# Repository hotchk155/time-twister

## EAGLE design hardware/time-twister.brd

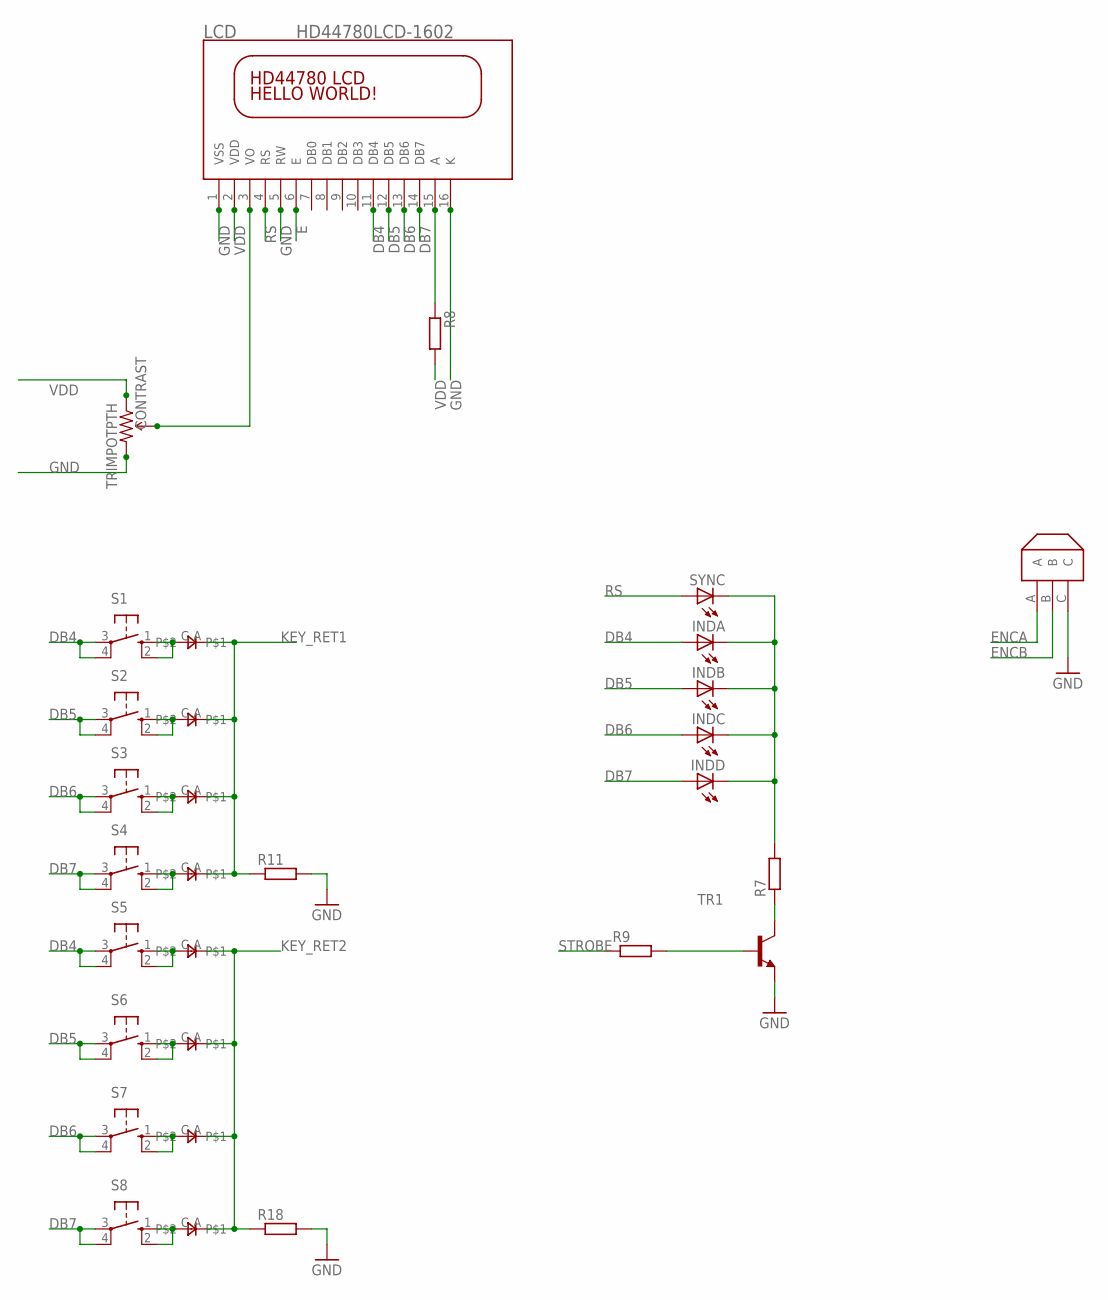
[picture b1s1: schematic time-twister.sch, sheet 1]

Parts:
CONTRAST: TRIMPOTPTH; TRIM_POT_PTH
D5, D6, D7, D8, D10, D11, D12, D13: 0805DIODE
ENC1: ENCODER
INDA: LED3MM
INDB: LED3MM
INDC: LED3MM
INDD: LED3MM
LCD: HD44780LCD-1602; LCD1602
R7, R8, R9, R11, R18: R-EU_R0805; R0805
S1, S2, S3, S4, S5, S6, S7, S8: 40-XX; B3F-40XX
SYNC: LED3MM
TR1: MMBT3904LT1-NPN-SOT23-BEC; SOT23-BEC

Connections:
DB4: INDA.A, LCD.11 (DB4), S1.3, S1.4 (P1), S5.3, S5.4 (P1); also elsewhere on the board
DB5: INDB.A, LCD.12 (DB5), S2.3, S2.4 (P1), S6.3, S6.4 (P1); also elsewhere on the board
DB6: INDC.A, LCD.13 (DB6), S3.3, S3.4 (P1), S7.3, S7.4 (P1); also elsewhere on the board
DB7: INDD.A, LCD.14 (DB7), S4.3, S4.4 (P1), S8.3, S8.4 (P1); also elsewhere on the board
E: LCD.6 (E); also elsewhere on the board
ENCA: ENC1.A; also elsewhere on the board
ENCB: ENC1.B; also elsewhere on the board
GND: CONTRAST.3 (CW), ENC1.C, LCD.1 (VSS), LCD.5 (RW), LCD.16 (K), R11.2, R18.2, TR1.E; also elsewhere on the board
INDC: INDA.K (C), INDB.K (C), INDC.K (C), INDD.K (C), R7.2, SYNC.K (C)
KEY_RET1: D10.A, D11.A, D12.A, D13.A, R11.1; also elsewhere on the board
KEY_RET2: D5.A, D6.A, D7.A, D8.A, R18.1; also elsewhere on the board
LCD_A: LCD.15 (A), R8.1
LCD_VO: CONTRAST.2 (WIPER), LCD.3 (VO)
unnamed: R7.1, TR1.C
unnamed: D12.C, S1.1 (S), S1.2 (S1)
unnamed: D10.C, S2.1 (S), S2.2 (S1)
unnamed: D13.C, S3.1 (S), S3.2 (S1)
unnamed: D11.C, S4.1 (S), S4.2 (S1)
unnamed: D8.C, S5.1 (S), S5.2 (S1)
unnamed: D7.C, S6.1 (S), S6.2 (S1)
unnamed: D6.C, S7.1 (S), S7.2 (S1)
unnamed: D5.C, S8.1 (S), S8.2 (S1)
unnamed: R9.2, TR1.B
RS: LCD.4 (RS), SYNC.A; also elsewhere on the board
STROBE: R9.1; also elsewhere on the board
VDD: CONTRAST.1 (CCW), LCD.2 (VDD), R8.2; also elsewhere on the board

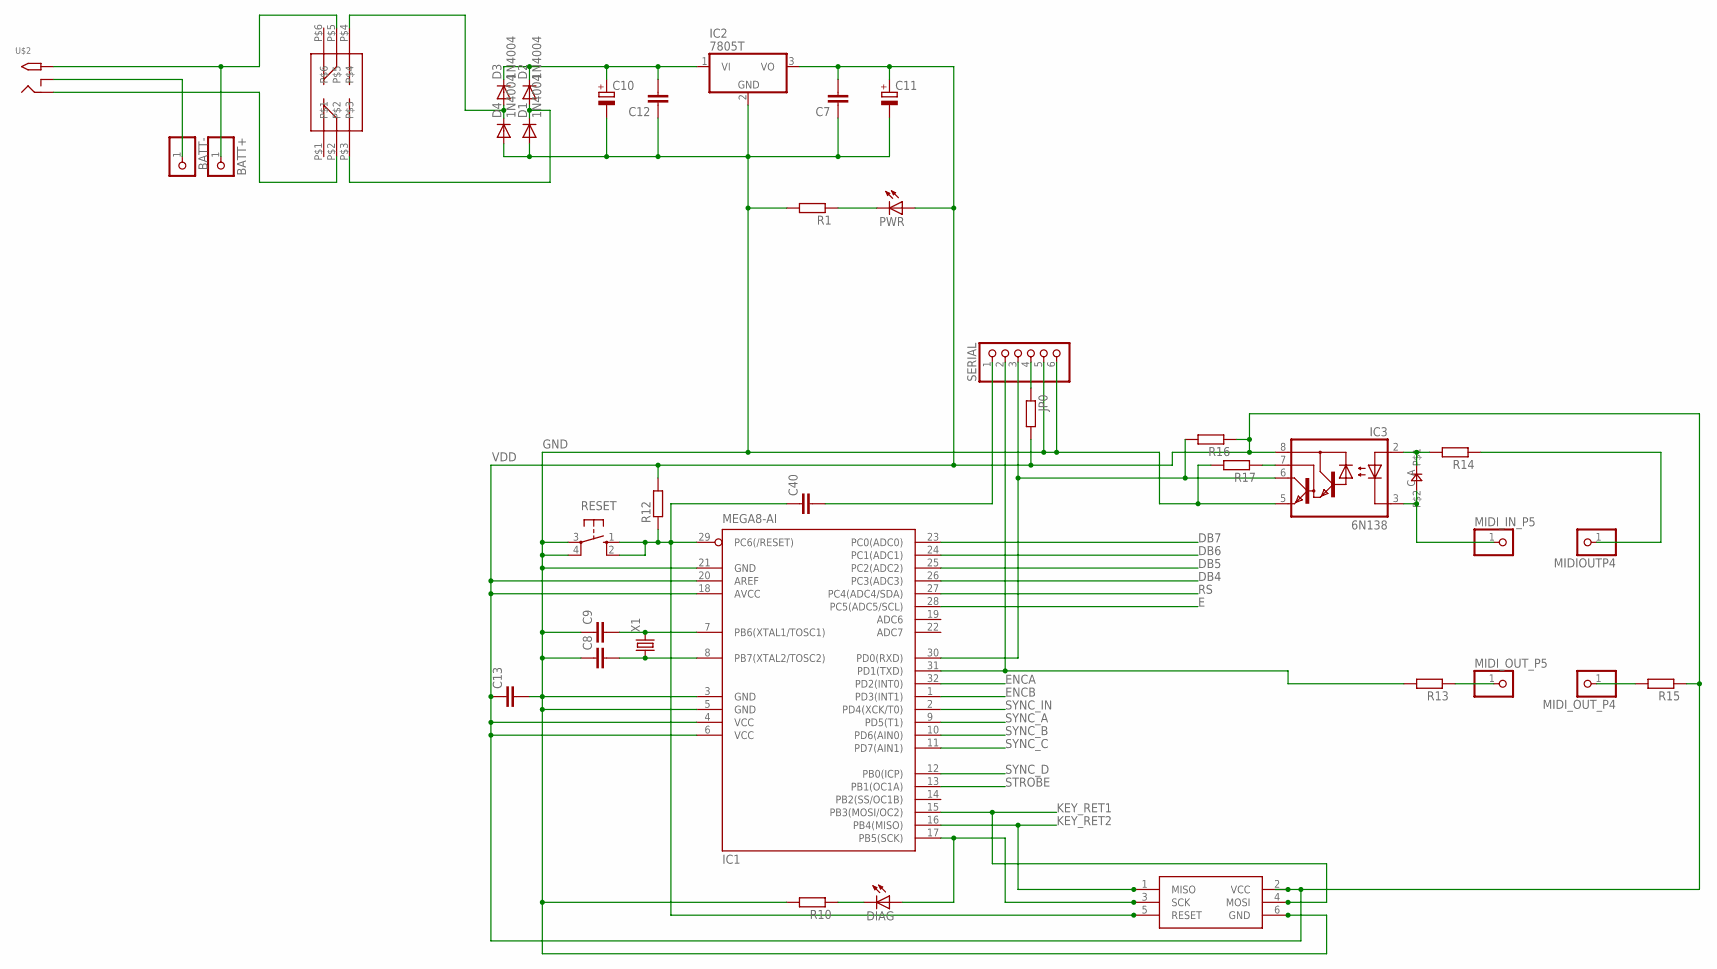
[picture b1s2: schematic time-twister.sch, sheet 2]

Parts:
BATT+: HEADER-1X1; 1X01_OVAL
BATT-: HEADER-1X1; 1X01_OVAL
C7, C8, C9, C12, C13, C40: C-EUC0805; C0805
C10, C11: CPOL-EUE2.5-6; E2,5-6
D1, D2, D3, D4: 1N4004; DO-VERT
D9: 0805DIODE
DIAG: LED3MM
IC1: MEGA8-AI; TQFP32-08
IC2: 7805T; TO220H
IC3: 6N138; DIL08
JP0: R-EU_R0805; R0805
MIDIOUTP4: HEADER-1X1; 1X01_OVAL
MIDI_IN_P5: HEADER-1X1; 1X01_OVAL
MIDI_OUT_P4, MIDI_OUT_P5: HEADER-1X1; 1X01_OVAL
ONOFF: 2P2T_LATCHING
PWR: LED3MM
R1, R10, R12, R13, R14, R15, R16, R17: R-EU_R0805; R0805
RESET: 10-XX; B3F-10XX
SERIAL: PINHD-1X6; 1X06
U$2: 2.1MMJACKTHM; PJ-102A
U$34: TAG_CONN_AVR; TC2030-MCP-NL
X1: CRYSTALHC49S; HC49/S

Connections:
BLINK: DIAG.A, IC1.17 (PB5(SCK)), U$34.3 (SCK)
DB4: IC1.26 (PC3(ADC3)); also elsewhere on the board
DB5: IC1.25 (PC2(ADC2)); also elsewhere on the board
DB6: IC1.24 (PC1(ADC1)); also elsewhere on the board
DB7: IC1.23 (PC0(ADC0)); also elsewhere on the board
E: IC1.28 (PC5(ADC5/SCL)); also elsewhere on the board
ENCA: IC1.32 (PD2(INT0)); also elsewhere on the board
ENCB: IC1.1 (PD3(INT1)); also elsewhere on the board
GND: C7.1, C8.1, C9.1, C10.-, C11.-, C12.1, C13.2, D1.A, D4.A, IC1.3 (GND), IC1.5 (GND), IC1.21 (GND), IC2.2 (GND), IC3.5 (GND), R1.2, R10.2, R17.2, RESET.3, RESET.4 (P1), SERIAL.5, SERIAL.6, U$34.6 (GND); also elsewhere on the board
KEY_RET1: IC1.15 (PB3(MOSI/OC2)), U$34.4 (MOSI); also elsewhere on the board
KEY_RET2: IC1.16 (PB4(MISO)), U$34.1 (MISO); also elsewhere on the board
MIDI_IN_4: MIDI_OUT_P4.1, R15.2
MIDI_IN_P4: MIDIOUTP4.1, R14.1
MIDI_OUT_5: D9.C, IC3.3 (C), MIDI_IN_P5.1
MIDI_OUT_P5: MIDI_OUT_P5.1, R13.1
unnamed: C9.2, IC1.7 (PB6(XTAL1/TOSC1)), X1.2
unnamed: C8.2, IC1.8 (PB7(XTAL2/TOSC2)), X1.1
unnamed: C40.1, IC1.29 (PC6(/RESET)), R12.1, RESET.1 (S), RESET.2 (S1), U$34.5 (RESET)
unnamed: JP0.1, SERIAL.4
unnamed: C40.2, SERIAL.1
unnamed: IC1.31 (PD1(TXD)), R13.2, SERIAL.2
unnamed: IC1.30 (PD0(RXD)), IC3.6 (VO), R16.2, SERIAL.3
unnamed: C10.+, C12.2, D2.C, D3.C, IC2.1 (VI)
unnamed: BATT+.1, ONOFF.P$5, U$2.TIP
unnamed: ONOFF.P$2, U$2.RING
unnamed: BATT-.1, U$2.RING_SW
unnamed: IC3.7 (VB), R17.1
unnamed: D9.A, IC3.2 (A), R14.2
unnamed: DIAG.K (C), R10.1
unnamed: PWR.K (C), R1.1
unnamed: D1.C, D2.A, ONOFF.P$3
unnamed: D3.A, D4.C, ONOFF.P$4
RS: IC1.27 (PC4(ADC4/SDA)); also elsewhere on the board
STROBE: IC1.13 (PB1(OC1A)); also elsewhere on the board
SYNC_A: IC1.9 (PD5(T1)); also elsewhere on the board
SYNC_B: IC1.10 (PD6(AIN0)); also elsewhere on the board
SYNC_C: IC1.11 (PD7(AIN1)); also elsewhere on the board
SYNC_D: IC1.12 (PB0(ICP)); also elsewhere on the board
SYNC_IN: IC1.2 (PD4(XCK/T0)); also elsewhere on the board
VDD: C7.2, C11.+, C13.1, IC1.4 (VCC), IC1.6 (VCC), IC1.18 (AVCC), IC1.20 (AREF), IC2.3 (VO), IC3.8 (VCC), JP0.2, PWR.A, R12.2, R15.1, R16.1, U$34.2 (VCC); also elsewhere on the board

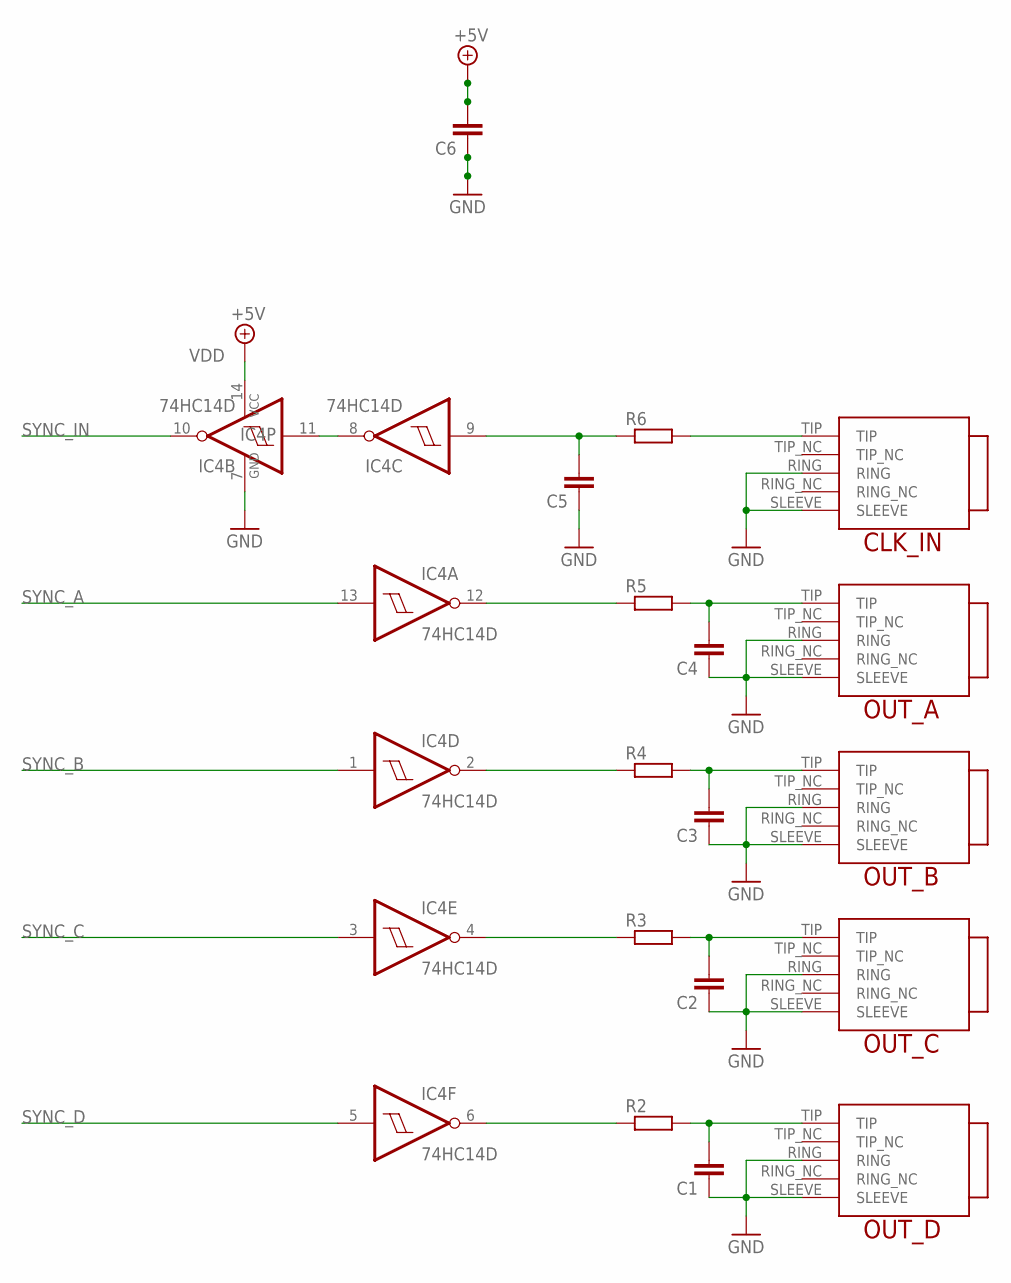
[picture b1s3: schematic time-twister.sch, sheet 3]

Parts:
C1, C2, C3, C4, C5, C6: C-EUC0805; C0805
CLK_IN: TRUCONNECTJACK
IC4: 74HC14D; SO14
OUT_A: TRUCONNECTJACK
OUT_B: TRUCONNECTJACK
OUT_C: TRUCONNECTJACK
OUT_D: TRUCONNECTJACK
R2, R3, R4, R5, R6: R-EU_M0805; M0805

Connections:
GND: C1.1, C2.1, C3.1, C4.1, C5.1, C6.1, CLK_IN.RING, CLK_IN.SLEEVE, IC4.7 (GND), OUT_A.RING, OUT_A.SLEEVE, OUT_B.RING, OUT_B.SLEEVE, OUT_C.RING, OUT_C.SLEEVE, OUT_D.RING, OUT_D.SLEEVE; also elsewhere on the board
unnamed: C3.2, OUT_B.TIP, R4.2
unnamed: C4.2, OUT_A.TIP, R5.2
unnamed: C2.2, OUT_C.TIP, R3.2
unnamed: C1.2, OUT_D.TIP, R2.2
unnamed: CLK_IN.TIP, R6.2
unnamed: C5.2, IC4.9 (I), R6.1
unnamed: IC4.8 (O), IC4.11 (I)
unnamed: IC4.6 (O), R2.1
unnamed: IC4.4 (O), R3.1
unnamed: IC4.2 (O), R4.1
unnamed: IC4.12 (O), R5.1
SYNC_A: IC4.13 (I); also elsewhere on the board
SYNC_B: IC4.1 (I); also elsewhere on the board
SYNC_C: IC4.3 (I); also elsewhere on the board
SYNC_D: IC4.5 (I); also elsewhere on the board
SYNC_IN: IC4.10 (O); also elsewhere on the board
VDD: C6.2, IC4.14 (VCC); also elsewhere on the board

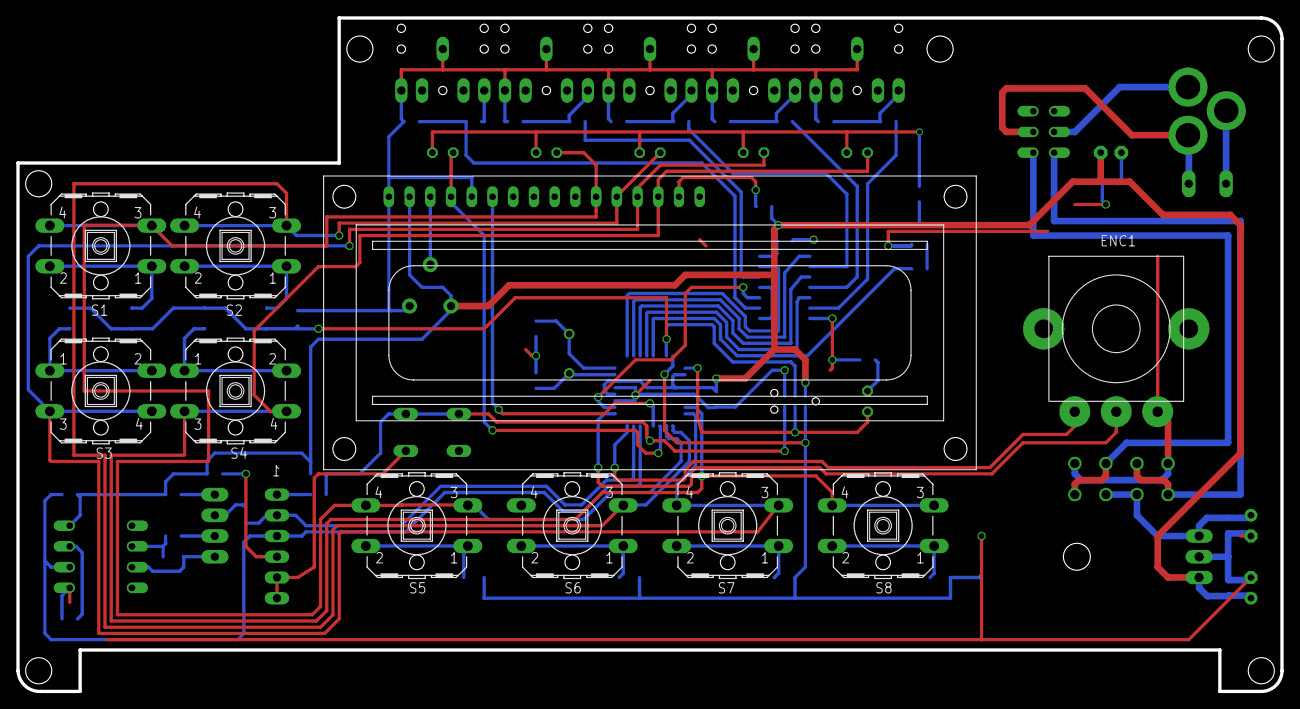
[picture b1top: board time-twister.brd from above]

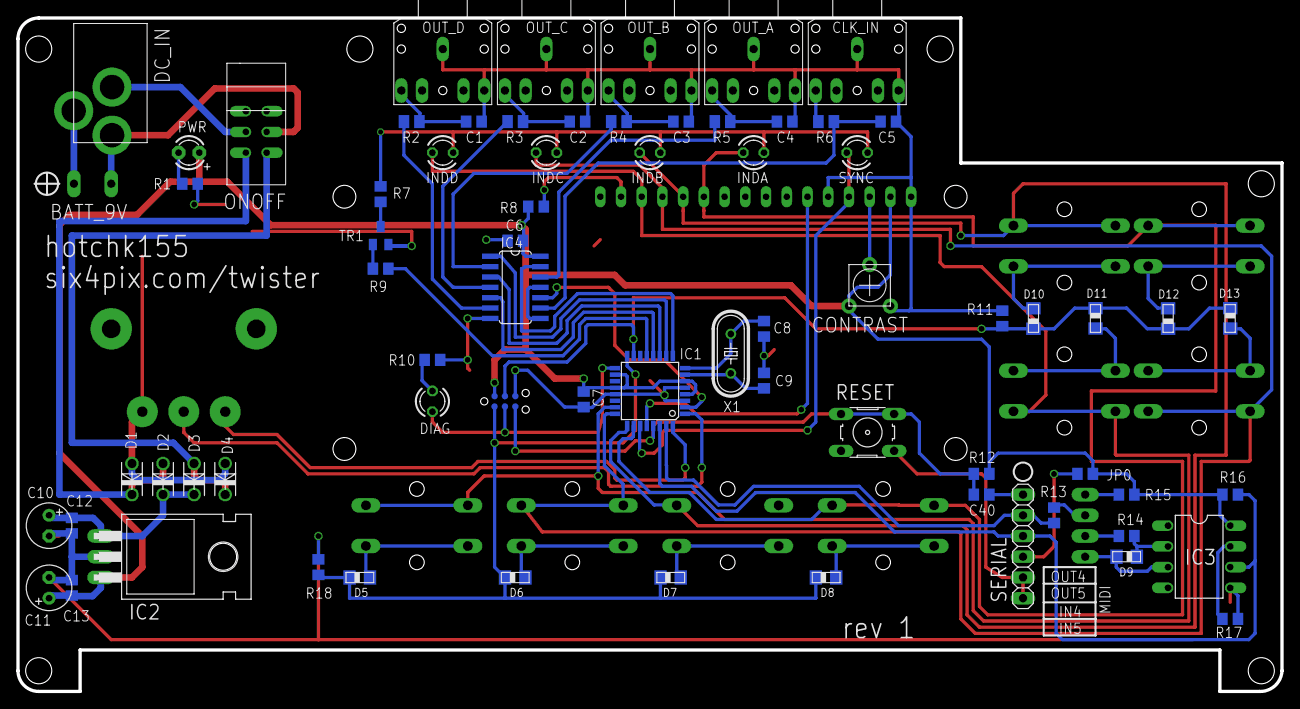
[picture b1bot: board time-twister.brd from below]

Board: 2 copper layers, 154.9 x 82.5 mm, 86 parts (74 on the bottom side), 64 nets.

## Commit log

2015-05-25 :boom::camel: Added .gitattributes & .gitignore files
2015-05-29 tweaks

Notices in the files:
parts and their libraries:
jasons_stuff: ©2009 ROFA.cz - modified and updated by Robert Darlington ‹rdarlington@gmail.com›
